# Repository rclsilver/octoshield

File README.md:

# OctoShield

This Raspberry pi hat can be used with [OctoPrint-Enclosure](https://plugins.octoprint.org/plugins/enclosure/) plugin.

This hat is compatible with Raspberry Pi 2, 3 or 4.

With this hat, you will be able to:
* manage a 30x30 5V fan to regulate the Raspberry Pi temperature
* manage a dual relay module for printer power and a LED strip
* read the temperature of your enclosure with a [DS18B20](https://datasheets.maximintegrated.com/en/ds/DS18B20.pdf) sensor
* cut the power of your printer when some smoke is detected by an external smoke detector or when you press an emergency button

All connectors are [JST XH](https://www.jst-mfg.com/product/pdf/eng/eXH.pdf) to be easier to use.

## Inputs / Outputs

* `GPIO.5` (Output): The fan
* `GPIO.7` (Input): The [DS18B20](https://datasheets.maximintegrated.com/en/ds/DS18B20.pdf) sensor
* `GPIO.27` (Input): The power button to toggle printer power
* `GPIO.17` (Output): The signal to the relay which manages the printer power
* `GPIO.4` (Input): The LED button to toggle LED strip power
* `GPIO.3` (Output): The signal to the relay which manages the LED strip power
* `GPIO. 6` (Input): The emergency signal to turn off the printer power

## Power

The board works with a *5V DC* power. The power supply must be connected to `J1` connector:

## Fan

The fan must be connected to `J3` connector:

The fan can be controlled with the `GPIO.5`. A *HIGH* level turn on the fan.

You can use the provided [script](/fan-control/fan-control.py) and [SystemD service](/fan-control/fan-control.service) to manage the regulate the temperature.

You must use the [SSH](https://www.raspberrypi.org/documentation/remote-access/ssh/) access to enable the service by executing following commands with the `pi` user:

```shell
git clone https://github.com/rclsilver/octoshield.git
sudo cp octoshield/fan-control/fan-control.py /usr/local/bin
sudo cp octoshield/fan-control/fan-control.service /etc/systemd/system/
sudo systemctl daemon-reload
sudo systemctl enable fan-control.service
sudo systemctl start fan-control.service
```

## Temperature sensor

The sensor must be connected to `J4` connector:

Temperature sensor [DS18B20](https://datasheets.maximintegrated.com/en/ds/DS18B20.pdf) can be used with the [1-Wire](https://en.wikipedia.org/wiki/1-Wire) protocol on a Raspberry Pi.

You must enable this interface to be used with the [SSH](https://www.raspberrypi.org/documentation/remote-access/ssh/) access by executing following commands with the `pi` user:

```shell
sudo raspi-config
```

*Note*: Use the direction arrows to navigate in the menu and the *Enter* key to validate.

1. Enter in the `Interfacing Options` menu

1. Enter in the `1-Wire` submenu

1. Select `Yes` and press the *Enter* key

1. The interface has been enabled, you can press *Enter* to continue

1. You can now select `Finish` with the *Right arrow* key

1. You have to reboot the Raspberry pi

You will need to obtain your temperature device id by executing the following command:

```shell
cat /sys/devices/w1_bus_master1/*/name
```

This will print the ID if all is working fine. If nothing is printed, please check your installation.

Now, in the [OctoPrint-Enclosure](https://plugins.octoprint.org/plugins/enclosure/) plugin settings, you can add your sensor by adding a new Input and following this screenshot:

## Printer power

The power switch must be connected to `J5` connector:

When `+5V` and `IN` pins are connected, a *LOW* level is transmitted to the `PWR` pin of `J9` and power of printer is turned on. In this case, `OUT` pin is powered by a *5V DC* power to turn on a light signal.

### OctoPrint

Now, in the [OctoPrint-Enclosure](https://plugins.octoprint.org/plugins/enclosure/) plugin settings, you can manage the printer power relay following those screenshots.

#### Input

#### Output

## LED strip power

The LED strip switch must be connected to `J8` connector:

When `+5V` and `IN` pins are connected, a *LOW* level is transmitted to the `LED` pin of `J9` and power of LED strip is turned on. In this case, `OUT` pin is powered by a *5V DC* power to turn on a light signal.

### OctoPrint

Now, in the [OctoPrint-Enclosure](https://plugins.octoprint.org/plugins/enclosure/) plugin settings, you can manage the LED strip power relay following those screenshots.

#### Input

#### Output

## Smoke detector / Emergency button

You can use both a smoke detector or an emergency button to power down the printer.

### Smoke detector

Most of detectors send *9V DC* power when it detects some smoke. You must find points on your and connect them on `J8` connector:

When the detector is detecting smoke, a *HIGH* level is transmitted to the `GPIO.6`. You have to tell OctoPrint to turn off the printer.

### Emergency button

The emergency button must be connected to `J7` connector:

When `+5V` and `IN` pins are connected, a *HIGH* level is transmitted to the `GPIO.6`. You have to tell OctoPrint to turn off the printer.

### OctoPrint

Now, in the [OctoPrint-Enclosure](https://plugins.octoprint.org/plugins/enclosure/) plugin settings, you can add your emergency input following this screenshot.

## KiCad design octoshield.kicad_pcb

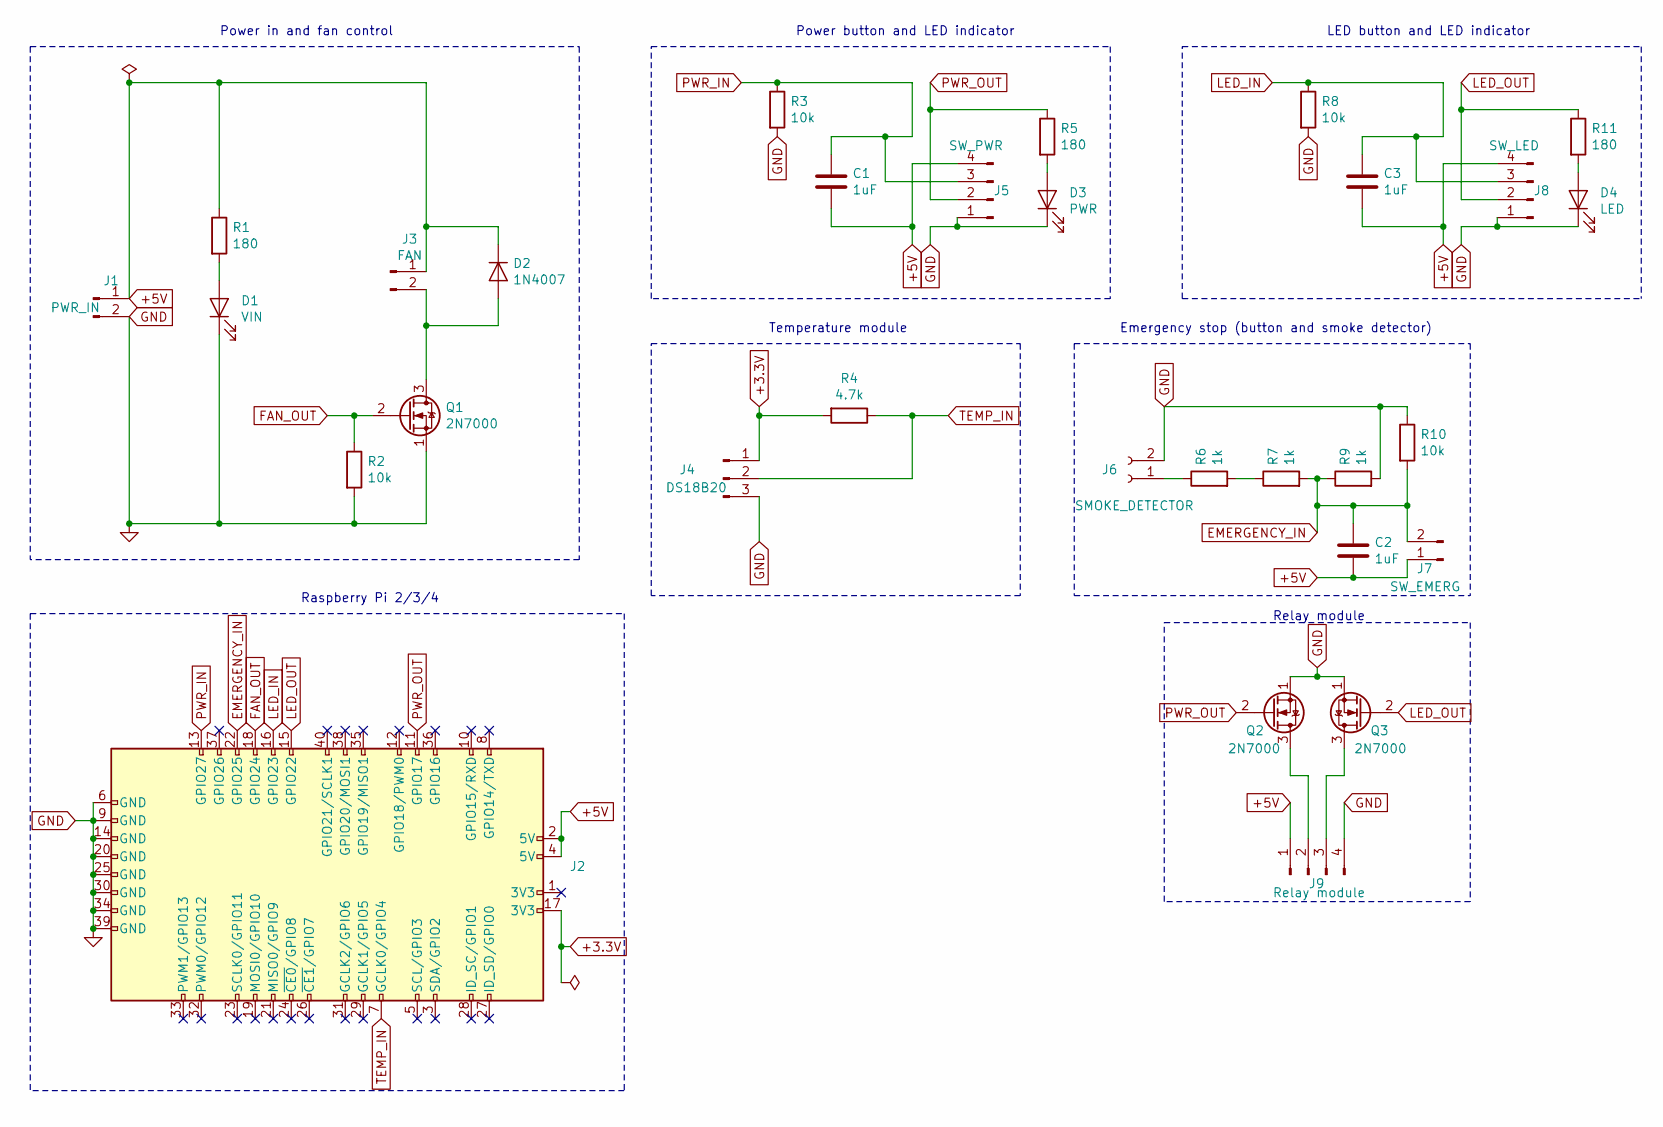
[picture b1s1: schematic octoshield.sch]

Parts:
C1, C2, C3: 1uF; C_1206_3216Metric_Pad1.42x1.75mm_HandSolder
D1: VIN; LED_1206_3216Metric_Pad1.42x1.75mm_HandSolder
D2: 1N4007; D_DO-41_SOD81_P10.16mm_Horizontal
D3: PWR; LED_1206_3216Metric_Pad1.42x1.75mm_HandSolder
D4: LED; LED_1206_3216Metric_Pad1.42x1.75mm_HandSolder
J1: PWR_IN; JST_XH_B2B-XH-A_1x02_P2.50mm_Vertical
J2: Raspberry Pi 2/3/4; PinSocket_2x20_P2.54mm_Vertical
J3: FAN; JST_XH_B2B-XH-A_1x02_P2.50mm_Vertical
J4: DS18B20; JST_XH_B3B-XH-A_1x03_P2.50mm_Vertical
J5: SW_PWR; JST_XH_B4B-XH-A_1x04_P2.50mm_Vertical
J6: SMOKE_DETECTOR; JST_XH_B2B-XH-A_1x02_P2.50mm_Vertical
J7: SW_EMERG; JST_XH_B2B-XH-A_1x02_P2.50mm_Vertical
J8: SW_LED; JST_XH_B4B-XH-A_1x04_P2.50mm_Vertical
J9: Relay module; JST_XH_B4B-XH-A_1x04_P2.50mm_Vertical
Q1, Q2, Q3: 2N7000; TO-92_Inline
R1, R5, R11: 180; R_1206_3216Metric_Pad1.42x1.75mm_HandSolder
R2, R3, R8, R10: 10k; R_1206_3216Metric_Pad1.42x1.75mm_HandSolder
R4: 4.7k; R_1206_3216Metric_Pad1.42x1.75mm_HandSolder
R6, R7, R9: 1k; R_1206_3216Metric_Pad1.42x1.75mm_HandSolder

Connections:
+3.3V: J2.17 (3V3), J4.1, R4.2
+5V: C1.2, C2.1, C3.2, D2.1 (K), J1.1, J2.2 (5V), J2.4 (5V), J3.1, J5.4, J7.1, J8.4, J9.1, R1.1
EMERGENCY_IN: C2.2, J2.22 (GPIO25), J7.2, R7.2, R9.1, R10.2
FAN_OUT: J2.18 (GPIO24), Q1.2 (G), R2.1
GND: D1.1 (K), D3.1 (K), D4.1 (K), J1.2, J2.6 (GND), J2.9 (GND), J2.14 (GND), J2.20 (GND), J2.25 (GND), J2.30 (GND), J2.34 (GND), J2.39 (GND), J4.3, J5.1, J6.2, J8.1, J9.4, Q1.1 (S), Q2.1 (S), Q3.1 (S), R2.2, R3.2, R8.2, R9.2, R10.1
LED_IN: C3.1, J2.16 (GPIO23), J8.3, R8.1
LED_OUT: J2.15 (GPIO22), J8.2, Q3.2 (G), R11.1
unnamed: D1.2 (A), R1.2
unnamed: D2.2 (A), J3.2, Q1.3 (D)
unnamed: D3.2 (A), R5.2
unnamed: D4.2 (A), R11.2
unnamed: J6.1, R6.1
unnamed: J9.2, Q2.3 (D)
unnamed: J9.3, Q3.3 (D)
unnamed: R6.2, R7.1
PWR_IN: C1.1, J2.13 (GPIO27), J5.3, R3.1
PWR_OUT: J2.11 (GPIO17), J5.2, Q2.2 (G), R5.1
TEMP_IN: J2.7 (GCLK0/GPIO4), J4.2, R4.1

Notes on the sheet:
Power button and LED indicator
LED button and LED indicator
Power in and fan control
Temperature module
Emergency stop (button and smoke detector)
Raspberry Pi 2/3/4
Relay module

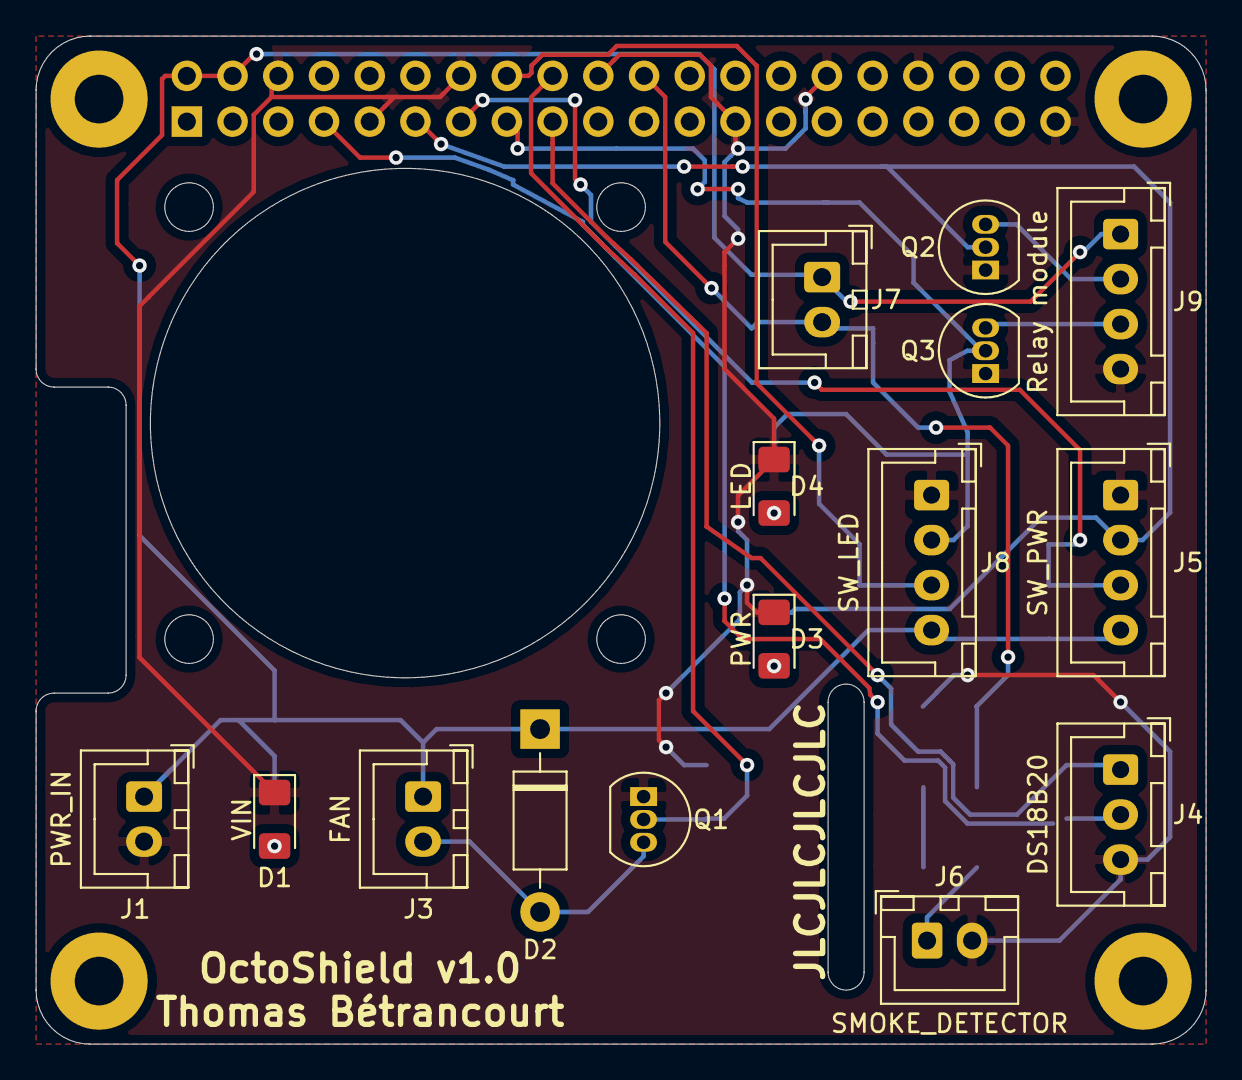
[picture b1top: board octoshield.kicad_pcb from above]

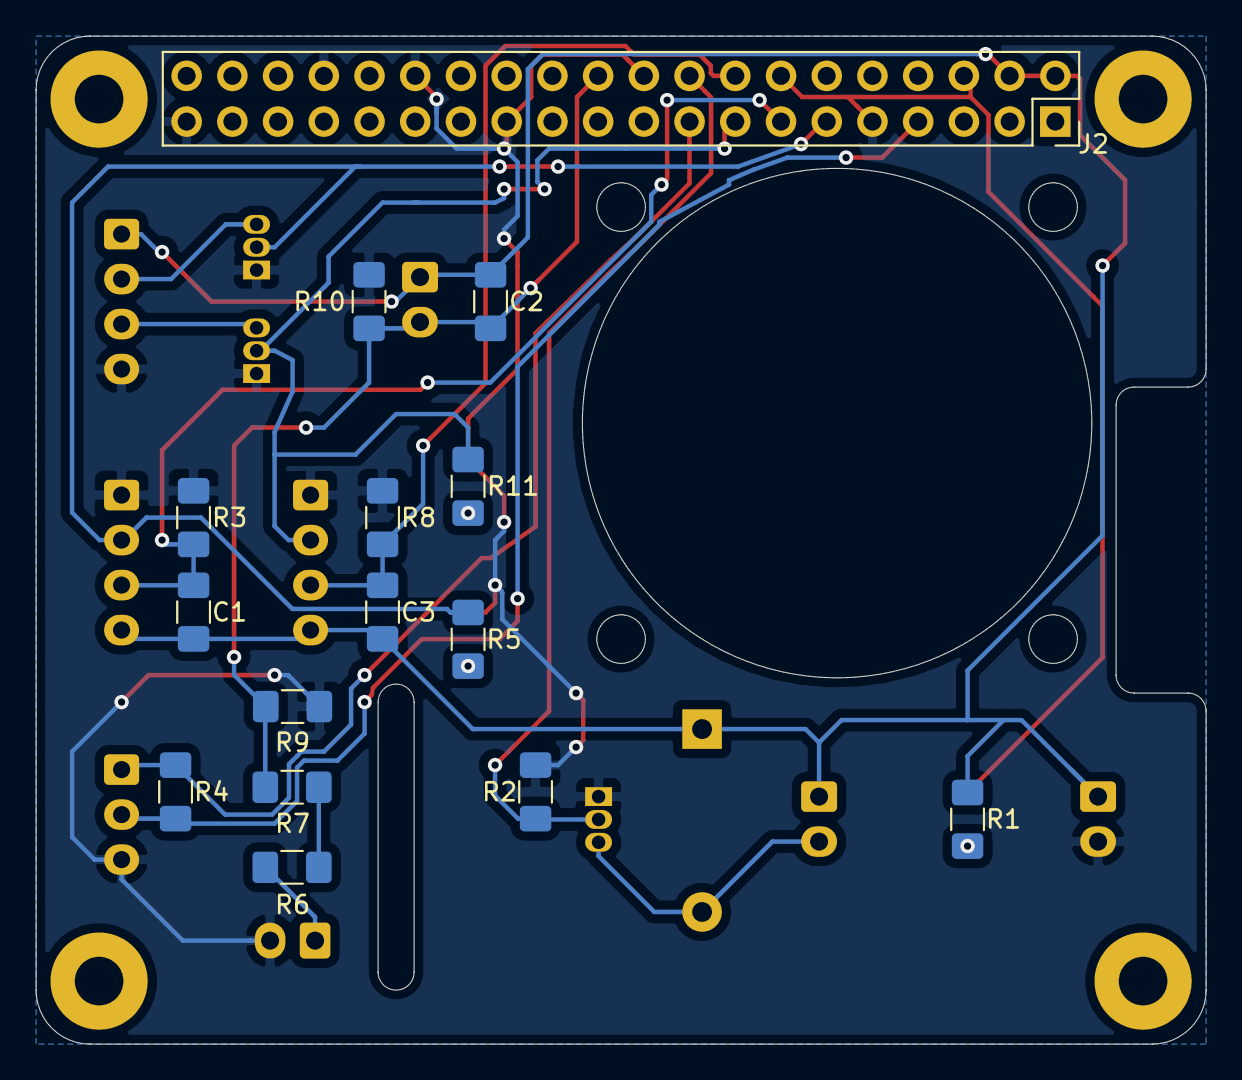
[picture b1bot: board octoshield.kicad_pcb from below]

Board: 2 copper layers, 65.0 x 56.0 mm, 30 parts (15 on the bottom side), 18 nets.

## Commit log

2020-05-23 Initial version
